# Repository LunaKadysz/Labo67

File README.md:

# Labo67
INTI, Metrology Department.

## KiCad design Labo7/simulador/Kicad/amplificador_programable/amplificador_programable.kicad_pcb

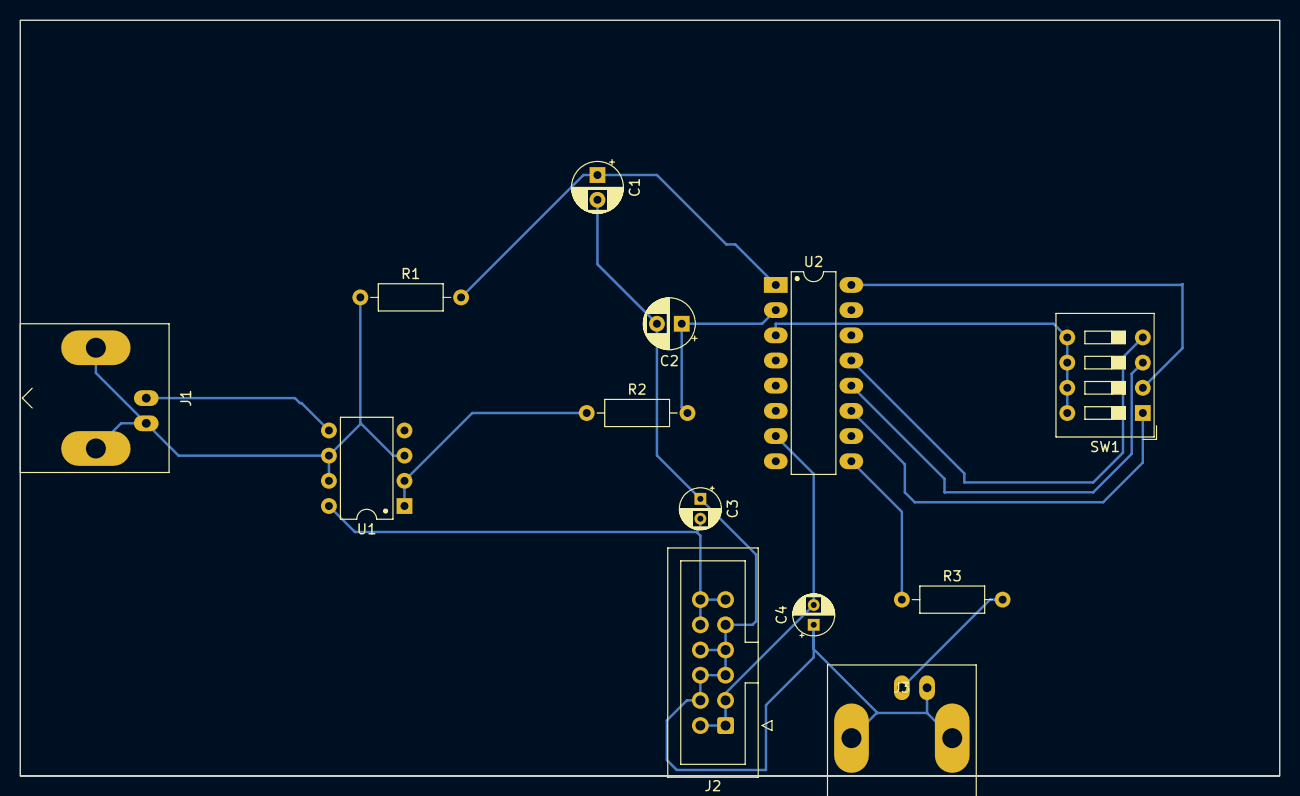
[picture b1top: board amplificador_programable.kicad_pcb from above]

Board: 2 copper layers, 127.0 x 76.2 mm, 13 parts (0 on the bottom side), 15 nets.

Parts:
C1, C2: C; CP_Radial_D5.0mm_P2.50mm
C3, C4: C; CP_Radial_D4.0mm_P2.00mm
J1, J3: Conn_Coaxial; BNC_Amphenol_B6252HB-NPP3G-50_Horizontal
J2: Conn_02x06_Counter_Clockwise; IDC-Header_2x06_P2.54mm_Vertical
R1, R2, R3: R; R_Axial_DIN0207_L6.3mm_D2.5mm_P10.16mm_Horizontal
SW1: SW_DIP_x04; SW_DIP_SPSTx04_Slide_9.78x12.34mm_W7.62mm_P2.54mm
U1: TL072; DIP-8_W7.62mm
U2: INA110KP; DIP-16_W7.62mm_LongPads

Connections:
Earth: C1.2, C2.2, C3.1, C4.1, J2.4, J2.5, J2.6, J2.7, J2.8, J2.9, J3.2 (Ext)
unnamed: J1.2 (Ext), R1.1, U1.3 (+), U1.6 (-), U1.7
unnamed: J1.1 (In), U1.5 (+)
unnamed: J3.1 (In), R3.2
unnamed: R3.1, U2.9
unnamed: R2.1, U1.1, U1.2 (-)
unnamed: C2.1, R2.2, U2.2 (+)
unnamed: C1.1, R1.2, U2.1 (-)
unnamed: SW1.4, U2.13 (G=10)
unnamed: SW1.3, U2.12 (G=100)
unnamed: SW1.2, U2.16 (G=200)
unnamed: SW1.1, U2.11 (G=500)
unnamed: SW1.5, SW1.6, SW1.7, SW1.8, U2.3 (RG)
VCC: C3.2, J2.10, J2.11, J2.12, U1.8 (V+), U2.8 (V+)
VDD: C4.2, J2.1, J2.2, J2.3, U1.4 (V-), U2.7 (V-)

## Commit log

2023-04-23 clase Muestras
2023-05-06 muestras
2023-05-10 funciona menos error
2023-05-14 arreglo muestras
2023-05-17 mediciones nitrogeno liquido
2023-05-22 modifs
2023-05-31 mediciones en nitrogeno 2.0
2023-06-05 mediciones nit plot
2023-06-08 plots
2023-06-08 mas plots
2023-06-12 caja cuantica
2023-06-14 biblio y plots
2023-06-21 corbino
2023-06-21 lockin
2023-06-26 ampli
2023-06-28 data ampli
2023-07-12 osciloscopio
2023-07-12 file
2023-07-31 informe
2023-09-19 labo7
2023-09-26 nuevo
2023-10-17 pcb, figs
2023-11-21 data simulacion
2023-11-27 simulacion
2023-11-28 data
2023-12-13 caracterizacion
